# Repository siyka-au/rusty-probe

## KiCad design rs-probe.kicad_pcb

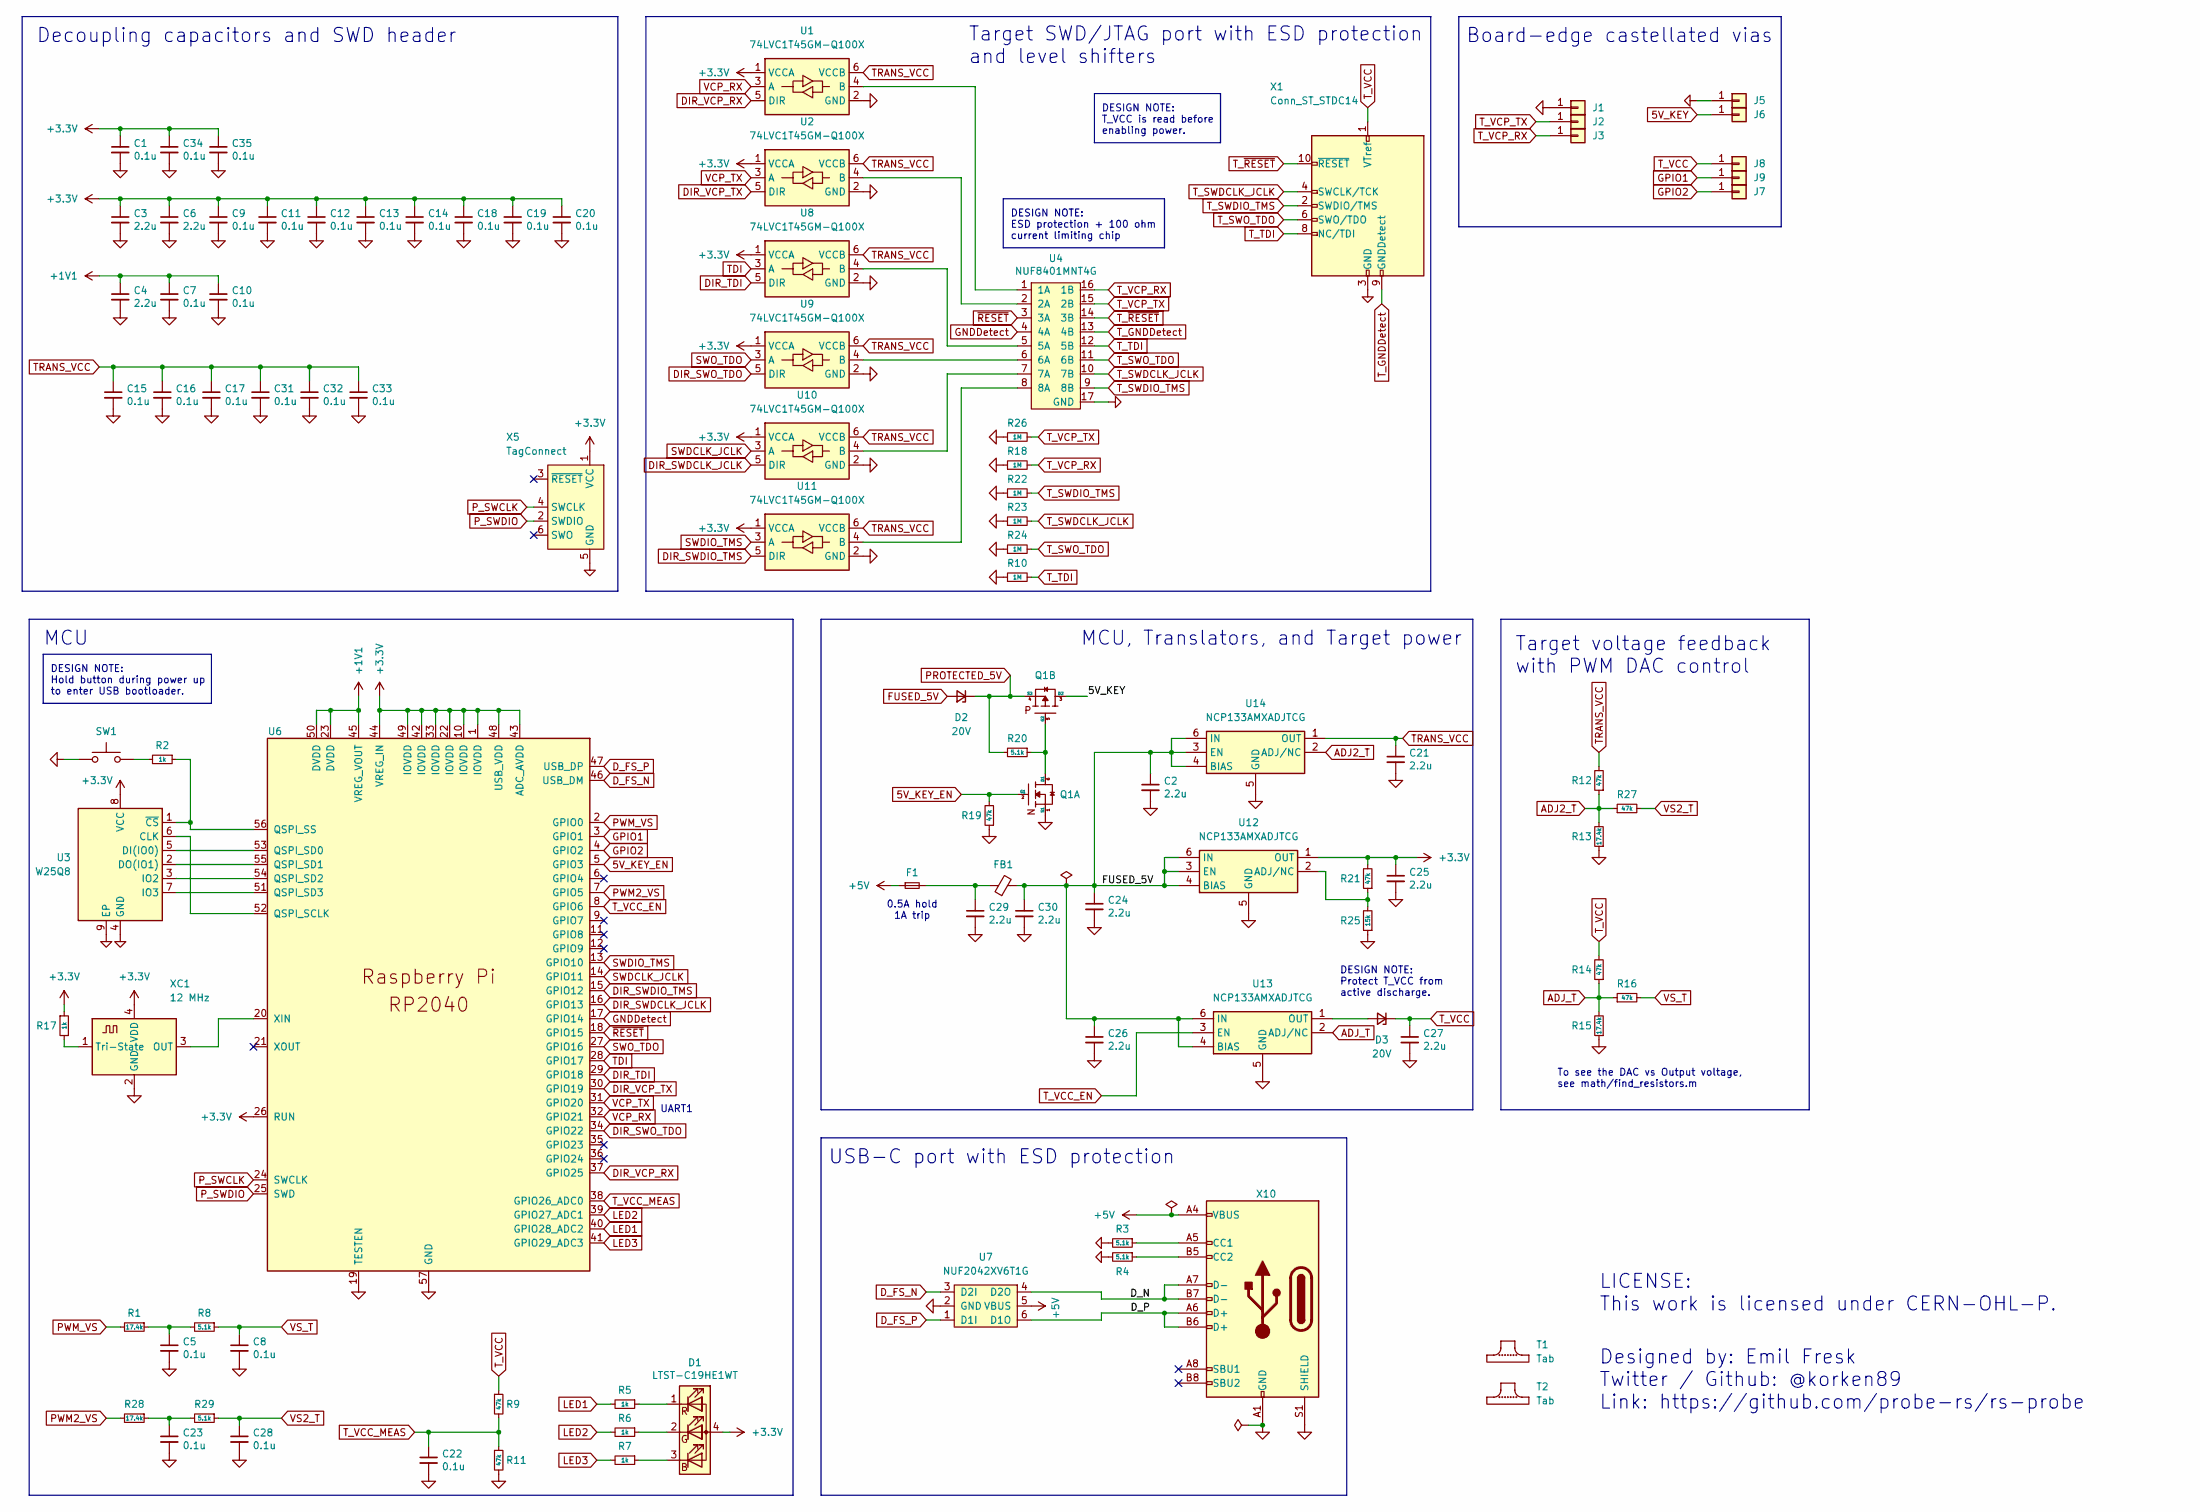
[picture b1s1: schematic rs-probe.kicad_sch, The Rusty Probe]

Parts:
C1, C5, C7, C8, C9, C10, C11, C12, C13, C14, C15, C16, C17, C18, C19, C20, C22, C23, C28, C31, C32, C33, C34, C35: 0.1u; C_0402; Tolerance 25V, X7R; LCSC C56392
C2, C3, C4, C6, C21, C24, C25, C26, C27, C29, C30: 2.2u; C_0402; Tolerance 10V, X5R; LCSC C77002
D1: LTST-C19HE1WT; LED_LiteOn_LTST-C19HE1WT; LCSC C427425, C458749
D2, D3: 20V; D_0402_1005Metric; LCSC C2837790
F1: Fuse_Small; Fuse_0603_1608Metric; LCSC C210357
FB1: BLM15AX601SN1D; R_0402; LCSC C76886
J1, J2, J3, J5, J6, J7, J8, J9: Conn_01x01; pad_2.0x2.5mm
Q1: NTZD3155C or CMLDM3757-TR-PBFREE or DMC2400UV-7 o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; SOT-563; LCSC C895156, C236117, C3280275, C177025, C2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
R1, R13, R15, R28: 17.4k; R_0402; Tolerance 1%; LCSC C409673
R2, R5, R6, R7, R17: 1k; R_0402; Tolerance 1%; LCSC C106235
R3, R4, R8, R20, R29: 5.1k; R_0402; Tolerance 1%; LCSC C105872
R9, R11, R12, R14, R16, R19, R21, R27: 47k; R_0402; Tolerance 1%; LCSC C144757
R10, R18, R22, R23, R24, R26: 1M; R_0402; Tolerance 1%; LCSC C138033
R25: 15k; R_0402; Tolerance 1%; LCSC C409673
SW1: EVQ-P2002W; PCB_JumperButton; LCSC C79148, C713481
T1, T2: Tab
U1, U2, U8, U9, U10, U11: 74LVC1T45GM-Q100X; SOT-886; LCSC C548481
U3: W25Q8; USON-8-3x2mm-EP; LCSC C2063555, C2759920, C2983691, C559220, 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
U4: NUF8401MNT4G; DFN-16-1EP_1.6x4mm_P0.5mm; LCSC C895158
U6: RP2040; RP2040-QFN-56; LCSC C2040
U7: NUF2042XV6T1G; SOT-563; LCSC C90707
U12, U13, U14: NCP133AMXADJTCG; DFN-6-1EP_1.2x1.2mm_P0.4mm_EP0.3x0.94mm_PullBack; LCSC C457672
X1: Conn_ST_STDC14; PinHeader_2x05_FTSH-105-01-L-DV-K; LCSC C448647
X5: TagConnect; Tag-Connect_TC2030-IDC-NL_2x03_P1.27mm_Vertical
X10: USB_C_Receptacle_USB2.0; USB_C_Receptacle_USB4105; LCSC C167321
XC1: 12 MHz; Crystal_SMD_2520-4Pin_2.5x2.0mm; LCSC C255991, C2681259, C3034288, C2901596

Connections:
5V_KEY: J6.1, Q1.3 (D2)
5V_KEY_EN: Q1.2 (G1), R19.2, U6.5 (GPIO3)
+1V1: C4.1, C7.1, C10.1, U6.23 (DVDD), U6.45 (VREG_VOUT), U6.50 (DVDD)
+3.3V: C1.1, C3.1, C6.1, C9.1, C11.1, C12.1, C13.1, C14.1, C18.1, C19.1, C20.1, C25.1, C34.1, C35.1, D1.4 (A), R17.1, R21.2, U1.1 (VCCA), U2.1 (VCCA), U3.8 (VCC), U6.1 (IOVDD), U6.10 (IOVDD), U6.22 (IOVDD), U6.26 (RUN), U6.33 (IOVDD), U6.42 (IOVDD), U6.43 (ADC_AVDD), U6.44 (VREG_IN), U6.48 (USB_VDD), U6.49 (IOVDD), U8.1 (VCCA), U9.1 (VCCA), U10.1 (VCCA), U11.1 (VCCA), U12.1 (OUT), X5.1 (VCC), XC1.4 (VDD)
+5V: F1.1, U7.5 (VBUS), X10.A4 (VBUS), X10.A9 (VBUS), X10.B4 (VBUS), X10.B9 (VBUS)
/D_N: U7.4 (D2O), X10.A7 (D-), X10.B7 (D-)
/D_P: U7.6 (D1O), X10.A6 (D+), X10.B6 (D+)
ADJ2_T: R12.1, R13.2, R27.1, U14.2 (ADJ/NC)
ADJ_T: R14.1, R15.2, R16.1, U13.2 (ADJ/NC)
DIR_SWDCLK_JCLK: U6.16 (GPIO13), U10.5 (DIR)
DIR_SWDIO_TMS: U6.15 (GPIO12), U11.5 (DIR)
DIR_SWO_TDO: U6.34 (GPIO22), U9.5 (DIR)
DIR_TDI: U6.29 (GPIO18), U8.5 (DIR)
DIR_VCP_RX: U1.5 (DIR), U6.37 (GPIO25)
DIR_VCP_TX: U2.5 (DIR), U6.30 (GPIO19)
D_FS_N: U6.46 (USB_DM), U7.3 (D2I)
D_FS_P: U6.47 (USB_DP), U7.1 (D1I)
FUSED_5V: C2.1, C24.1, C26.1, C30.1, D2.2 (A), FB1.2, U12.3 (EN), U12.4 (BIAS), U12.6 (IN), U13.4 (BIAS), U13.6 (IN), U14.3 (EN), U14.4 (BIAS), U14.6 (IN)
GND: C1.2, C2.2, C3.2, C4.2, C5.2, C6.2, C7.2, C8.2, C9.2, C10.2, C11.2, C12.2, C13.2, C14.2, C15.2, C16.2, C17.2, C18.2, C19.2, C20.2, C21.2, C22.2, C23.2, C24.2, C25.2, C26.2, C27.2, C28.2, C29.2, C30.2, C31.2, C32.2, C33.2, C34.2, C35.2, J1.1, J5.1, Q1.1 (S1), R3.2, R4.2, R10.1, R11.2, R13.1, R15.1, R18.1, R19.1, R22.1, R23.1, R24.1, R25.1, R26.1, SW1.1, U1.2 (GND), U2.2 (GND), U3.4 (GND), U3.9 (EP), U4.17 (GND), U6.19 (TESTEN), U6.57 (GND), U7.2 (GND), U8.2 (GND), U9.2 (GND), U10.2 (GND), U11.2 (GND), U12.5 (GND), U12.7 (GND), U13.5 (GND), U13.7 (GND), U14.5 (GND), U14.7 (GND), X1.3 (GND), X1.5 (GND), X5.5 (GND), X10.A1 (GND), X10.A12 (GND), X10.B1 (GND), X10.B12 (GND), X10.S1 (SHIELD), XC1.2 (GND)
GNDDetect: U4.4 (4A), U6.17 (GPIO14)
GPIO1: J9.1, U6.3 (GPIO1)
GPIO2: J7.1, U6.4 (GPIO2)
LED1: R5.2, U6.40 (GPIO28_ADC2)
LED2: R6.2, U6.39 (GPIO27_ADC1)
LED3: R7.2, U6.41 (GPIO29_ADC3)
unnamed: C5.1, R1.1, R8.2
unnamed: C23.1, R28.1, R29.2
unnamed: C29.1, F1.2, FB1.1
unnamed: D1.3 (BK), R7.1
unnamed: D1.2 (GK), R6.1
unnamed: D1.1 (RK), R5.1
unnamed: D3.2 (A), U13.1 (OUT)
unnamed: Q1.5 (G2), Q1.6 (D1), R20.1
unnamed: R2.2, SW1.2
unnamed: U1.4 (B), U4.1 (1A)
unnamed: U2.4 (B), U4.2 (2A)
unnamed: U3.6 (CLK), U6.52 (QSPI_SCLK)
unnamed: U3.5 (DI(IO0)), U6.53 (QSPI_SD0)
unnamed: U3.2 (DO(IO1)), U6.55 (QSPI_SD1)
unnamed: U3.3 (IO2), U6.54 (QSPI_SD2)
unnamed: U3.7 (IO3), U6.51 (QSPI_SD3)
unnamed: R2.1, U3.1 (~CS), U6.56 (QSPI_SS)
unnamed: U4.5 (5A), U8.4 (B)
unnamed: U4.6 (6A), U9.4 (B)
unnamed: U6.20 (XIN), XC1.3 (OUT)
unnamed: U4.7 (7A), U10.4 (B)
unnamed: U4.8 (8A), U11.4 (B)
unnamed: R21.1, R25.2, U12.2 (ADJ/NC)
unnamed: R3.1, X10.A5 (CC1)
unnamed: R4.1, X10.B5 (CC2)
unnamed: R17.2, XC1.1 (Tri-State)
PROTECTED_5V: D2.1 (K), Q1.4 (S2), R20.2
PWM2_VS: R28.2, U6.7 (GPIO5)
PWM_VS: R1.2, U6.2 (GPIO0)
P_SWCLK: U6.24 (SWCLK), X5.4 (SWCLK)
P_SWDIO: U6.25 (SWD), X5.2 (SWDIO)
SWDCLK_JCLK: U6.14 (GPIO11), U10.3 (A)
SWDIO_TMS: U6.13 (GPIO10), U11.3 (A)
SWO_TDO: U6.27 (GPIO16), U9.3 (A)
TDI: U6.28 (GPIO17), U8.3 (A)
TRANS_VCC: C15.1, C16.1, C17.1, C21.1, C31.1, C32.1, C33.1, R12.2, U1.6 (VCCB), U2.6 (VCCB), U8.6 (VCCB), U9.6 (VCCB), U10.6 (VCCB), U11.6 (VCCB), U14.1 (OUT)
T_GNDDetect: U4.13 (4B), X1.9 (GNDDetect)
T_SWDCLK_JCLK: R23.2, U4.10 (7B), X1.4 (SWCLK/TCK)
T_SWDIO_TMS: R22.2, U4.9 (8B), X1.2 (SWDIO/TMS)
T_SWO_TDO: R24.2, U4.11 (6B), X1.6 (SWO/TDO)
T_TDI: R10.2, U4.12 (5B), X1.8 (NC/TDI)
T_VCC: C27.1, D3.1 (K), J8.1, R9.1, R14.2, X1.1 (VTref)
T_VCC_EN: U6.8 (GPIO6), U13.3 (EN)
T_VCC_MEAS: C22.1, R9.2, R11.1, U6.38 (GPIO26_ADC0)
T_VCP_RX: J3.1, R18.2, U4.16 (1B)
T_VCP_TX: J2.1, R26.2, U4.15 (2B)
T_~RESET: U4.14 (3B), X1.10 (~RESET)
VCP_RX: U1.3 (A), U6.32 (GPIO21)
VCP_TX: U2.3 (A), U6.31 (GPIO20)
VS2_T: C28.1, R27.2, R29.1
VS_T: C8.1, R8.1, R16.2
~RESET: U4.3 (3A), U6.18 (GPIO15)

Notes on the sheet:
Designed by: Emil Fresk Twitter / Github: @korken89 Link: https://github.com/probe-rs/rs-probe
Target SWD/JTAG port with ESD protection and level shifters
Target voltage feedback with PWM DAC control
To see the DAC vs Output voltage, see math/find_resistors.m
USB-C port with ESD protection
DESIGN NOTE: T_VCC is read before enabling power.
Board-edge castellated vias
DESIGN NOTE: ESD protection + 100 ohm current limiting chip
Decoupling capacitors and SWD header
MCU
0.5A hold 1A trip
MCU, Translators, and Target power
DESIGN NOTE: Protect T_VCC from active discharge.
DESIGN NOTE: Hold button during power up to enter USB bootloader.
UART1
LICENSE: This work is licensed under CERN-OHL-P.

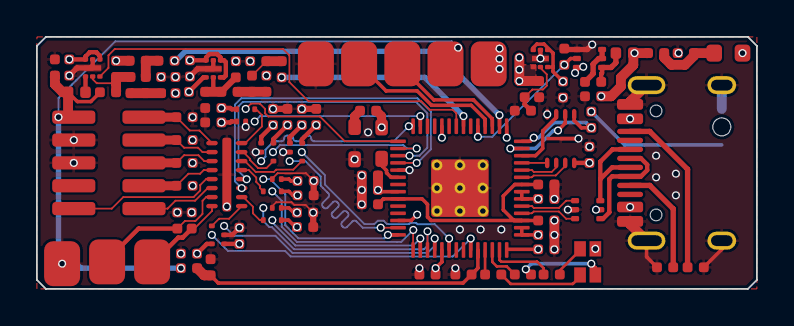
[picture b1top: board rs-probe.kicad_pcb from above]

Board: 4 copper layers, 40.0 x 14.0 mm, 97 parts (1 on the bottom side), 75 nets.

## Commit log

2024-06-19 Lots of work
2024-06-21 updating gitignore
2024-06-21 removing submodule
2024-06-21 moving kicad library from submodule into repository prior to cleanout
2024-06-21 clearing drc errors
2024-06-23 fixing missing 3D models
2024-07-16 deleted all silkscreens and generated some gerbers
